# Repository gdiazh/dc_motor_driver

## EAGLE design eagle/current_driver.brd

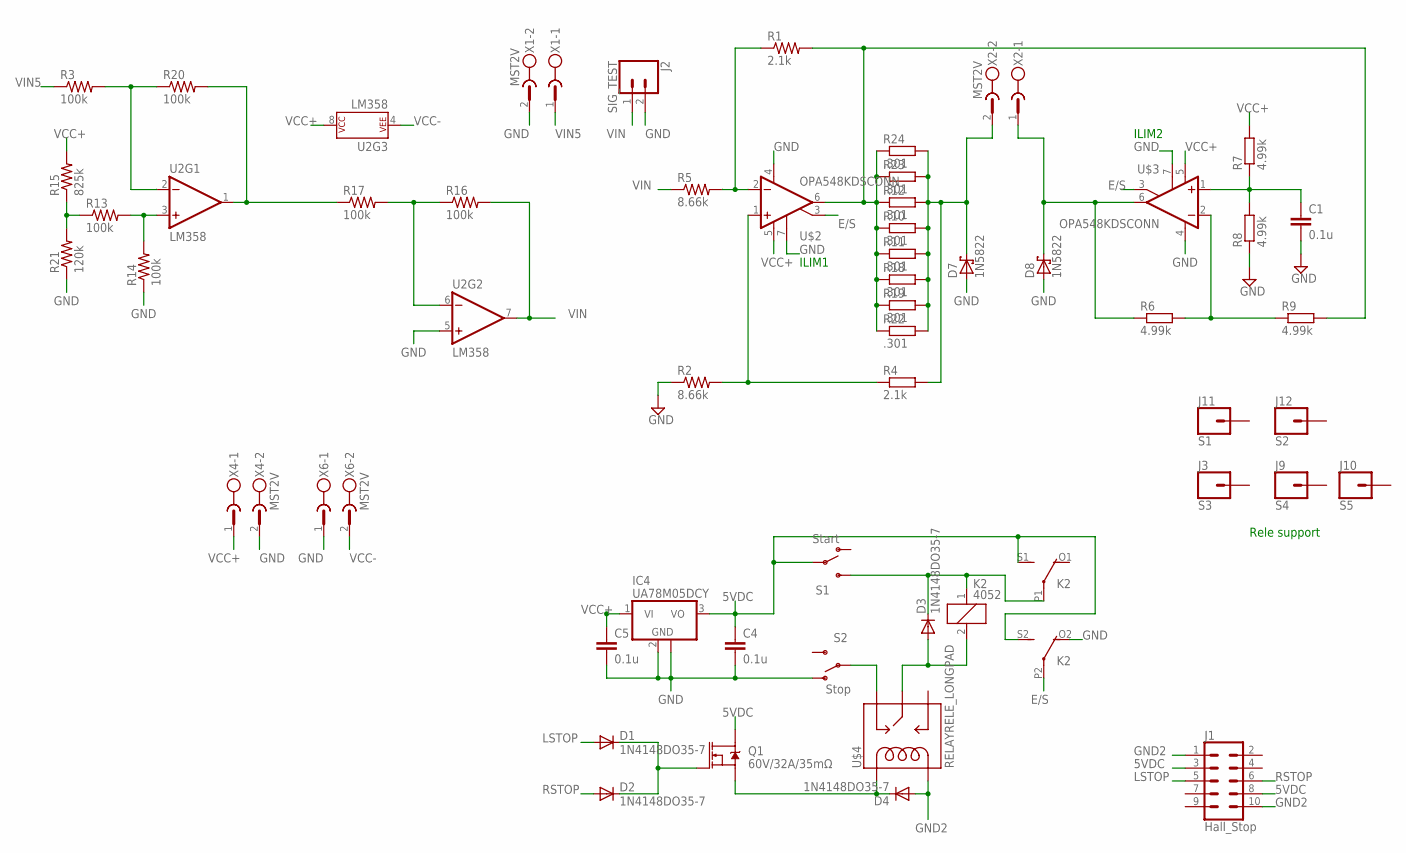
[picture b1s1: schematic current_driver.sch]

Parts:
C1, C4, C5: 0.1u; C2012
D1, D2, D3, D4: 1N4148DO35-7; DO35-7
D7, D8: 1N5822; F126Z12
IC4: UA78M05DCY; SOT223
J1: Hall_Stop; 2X5-SHROUDED_LOCK
J2: SIG_TEST; 1X02_LOCK_LONGPADS
J3: S3; 1X01_LONGPAD
J9: S4; 1X01_LONGPAD
J10: S5; 1X01_LONGPAD
J11: S1; 1X01_LONGPAD
J12: S2; 1X01_LONGPAD
K2: 4052; F4052
Q1: 60V/32A/35mΩ; TO220V
R1, R4: 2.1k; R0805
R2, R5: 8.66k; R0805
R3, R13, R14, R16, R17, R20: 100k; R0805
R6, R7, R8, R9: 4.99k; R0805
R10, R11, R12, R18, R19, R22, R23, R24: .301; M1206
R15: 825k; R0805
R21: 120k; R0805
S1: Start; SWITCH_SPDT_SMD
S2: Stop; SWITCH_SPDT_SMD
U2: LM358; DIP08_LONGPAD
U$2, U$3: OPA548KDSCONN
U$4: RELAYRELE_LONGPAD; RELE_LONGPAD
X1, X2, X4, X6: MST2V; MSTBV2

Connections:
5VDC: C4.1, IC4.3 (VO), J1.3, J1.8, K2.S1 (S), K2.S2 (S), Q1.2 (D), S1.2
E/S: K2.P2, U$2.3 (ILIM), U$3.3 (ILIM)
GND: C1.2, C4.2, C5.2, D7.A, D8.A, IC4.2 (GND), IC4.4 (GND), J2.2, K2.O2 (O), R2.1, R8.1, R14.1, R21.1, S2.1 (O), U2.5 (+IN), U$2.4 (V-), U$2.7 (E/S), U$3.4 (V-), U$3.7 (E/S), X1.2, X4.2, X6.1
GND2: D4.A, J1.1, J1.10, U$4.COIL0
LSTOP: D1.A, J1.5
unnamed: R1.1, R5.2, U$2.2 (-IN)
unnamed: D7.C, R4.2, R10.2, R11.2, R12.2, R18.2, R19.2, R22.2, R23.2, R24.2, X2.2
unnamed: R2.2, R4.1, U$2.1 (+IN)
unnamed: D8.C, R6.1, U$3.6 (OUT), X2.1
unnamed: R6.2, R9.1, U$3.2 (-IN)
unnamed: C1.1, R7.1, R8.2, U$3.1 (+IN)
unnamed: D3.C, K2.1, K2.P1, S1.3 (S)
unnamed: D4.C, Q1.3 (S), U$4.COIL1
unnamed: D3.A, K2.2, U$4.SWCOMMON
unnamed: S2.2, U$4.SWCLOSED (SWCLOSE)
unnamed: R17.1, R20.2, U2.1 (OUT)
unnamed: R3.2, R20.1, U2.2 (-IN)
unnamed: R13.2, R14.2, U2.3 (+IN)
unnamed: R13.1, R15.1, R21.2
unnamed: D1.C, D2.C, Q1.1 (G)
unnamed: R16.1, R17.2, U2.6 (-IN)
unnamed: R1.2, R9.2, R10.1, R11.1, R12.1, R18.1, R19.1, R22.1, R23.1, R24.1, U$2.6 (OUT)
RSTOP: D2.A, J1.6
VCC+: C5.1, IC4.1 (VI), R7.2, R15.2, U2.8 (P$V+), U$2.5 (V+), U$3.5 (V+), X4.1
VCC-: U2.4 (P$V-), X6.2
VIN: J2.1, R5.1, R16.2, U2.7 (OUT)
VIN5: R3.1, X1.1

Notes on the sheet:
ILIM1
ILIM2
Rele support

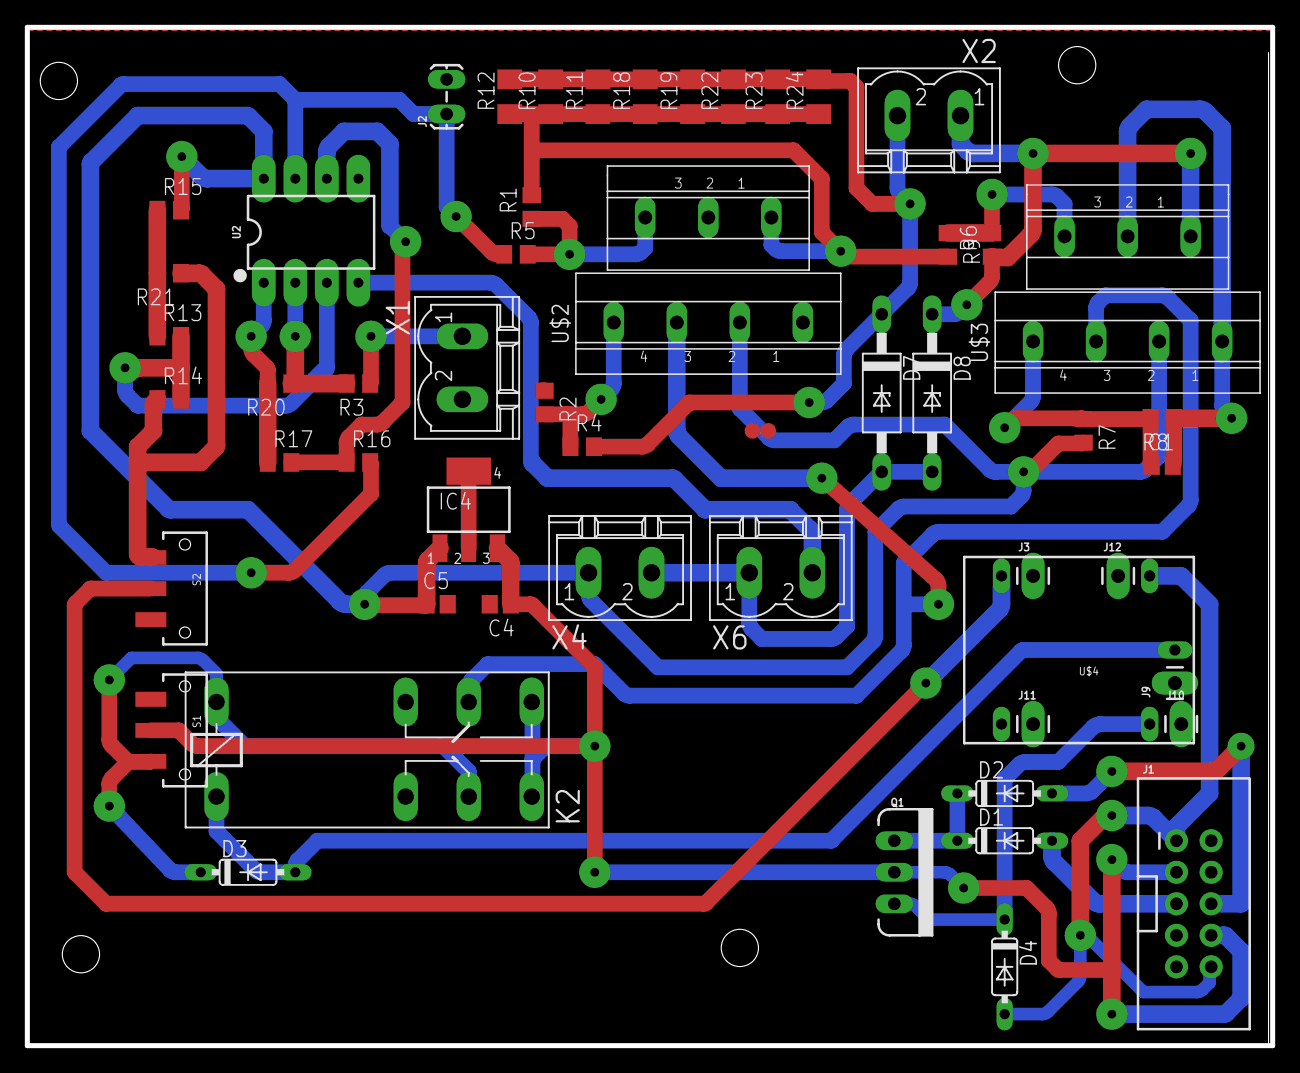
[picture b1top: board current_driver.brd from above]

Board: 2 copper layers, 100.3 x 82.0 mm, 53 parts (0 on the bottom side), 27 nets.

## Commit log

2017-05-25 start tracking the project
2017-11-19 modified Rs current sense resistor footprint

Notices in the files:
parts and their libraries:
SparkFun-Connectors: Licensing: Creative Commons ShareAlike 4.0 International - https://creativecommons.org/licenses/by-sa/4.0
